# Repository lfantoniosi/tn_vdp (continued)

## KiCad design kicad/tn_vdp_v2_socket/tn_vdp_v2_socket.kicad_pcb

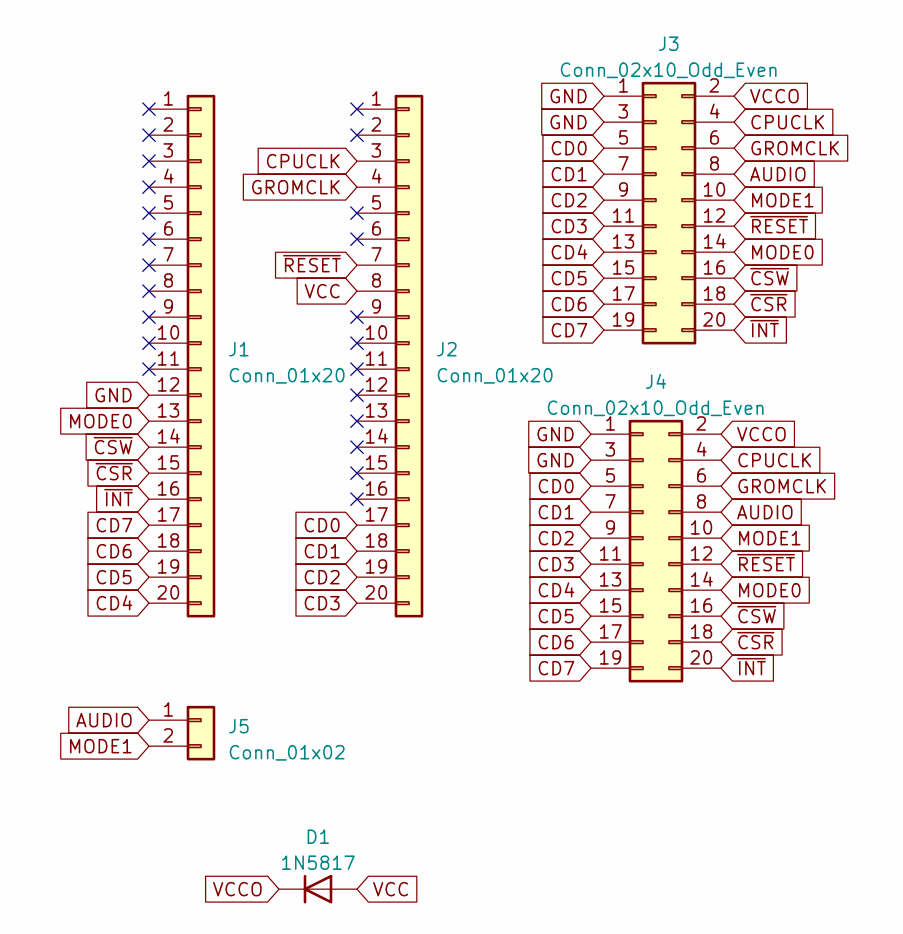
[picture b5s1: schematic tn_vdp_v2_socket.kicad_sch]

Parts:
D1: 1N5817; D_DO-41_SOD81_P10.16mm_Horizontal
J1, J2: Conn_01x20; PinHeader_1x20_P2.54mm_Vertical
J3, J4: Conn_02x10_Odd_Even; PinHeader_2x10_P2.54mm_Vertical
J5: Conn_01x02; PinHeader_1x02_P2.54mm_Vertical

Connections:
AUDIO: J3.8, J4.8, J5.1
CD0: J2.17, J3.5, J4.5
CD1: J2.18, J3.7, J4.7
CD2: J2.19, J3.9, J4.9
CD3: J2.20, J3.11, J4.11
CD4: J1.20, J3.13, J4.13
CD5: J1.19, J3.15, J4.15
CD6: J1.18, J3.17, J4.17
CD7: J1.17, J3.19, J4.19
CPUCLK: J2.3, J3.4, J4.4
GND: J1.12, J3.1, J3.3, J4.1, J4.3
GROMCLK: J2.4, J3.6, J4.6
MODE0: J1.13, J3.14, J4.14
MODE1: J3.10, J4.10, J5.2
VCC: D1.2 (A), J2.8
VCCO: D1.1 (K), J3.2, J4.2
~CSR: J1.15, J3.18, J4.18
~CSW: J1.14, J3.16, J4.16
~INT: J1.16, J3.20, J4.20
~RESET: J2.7, J3.12, J4.12

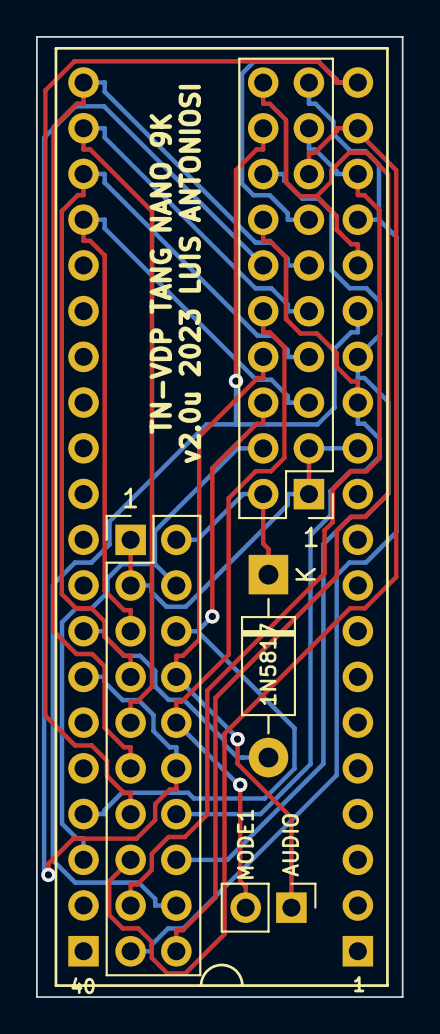
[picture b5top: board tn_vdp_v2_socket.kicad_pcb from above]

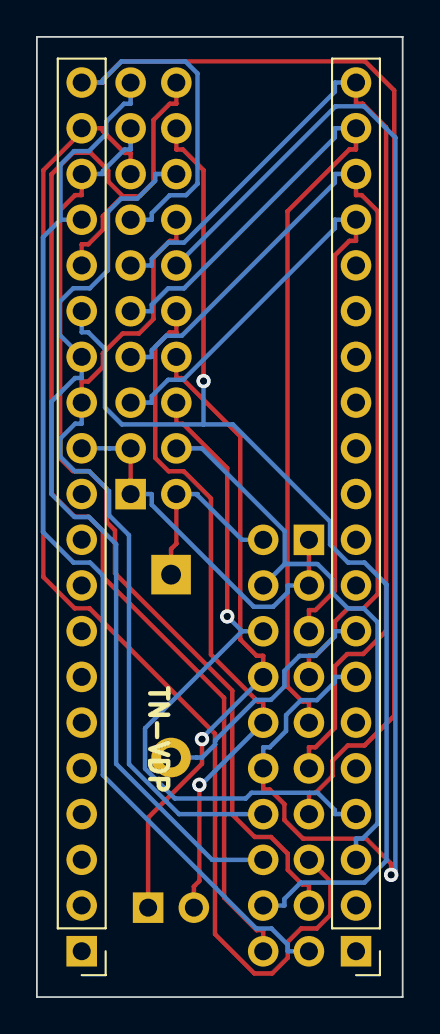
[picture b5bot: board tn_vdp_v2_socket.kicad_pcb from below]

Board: 2 copper layers, 20.3 x 53.3 mm, 6 parts (2 on the bottom side), 20 nets.

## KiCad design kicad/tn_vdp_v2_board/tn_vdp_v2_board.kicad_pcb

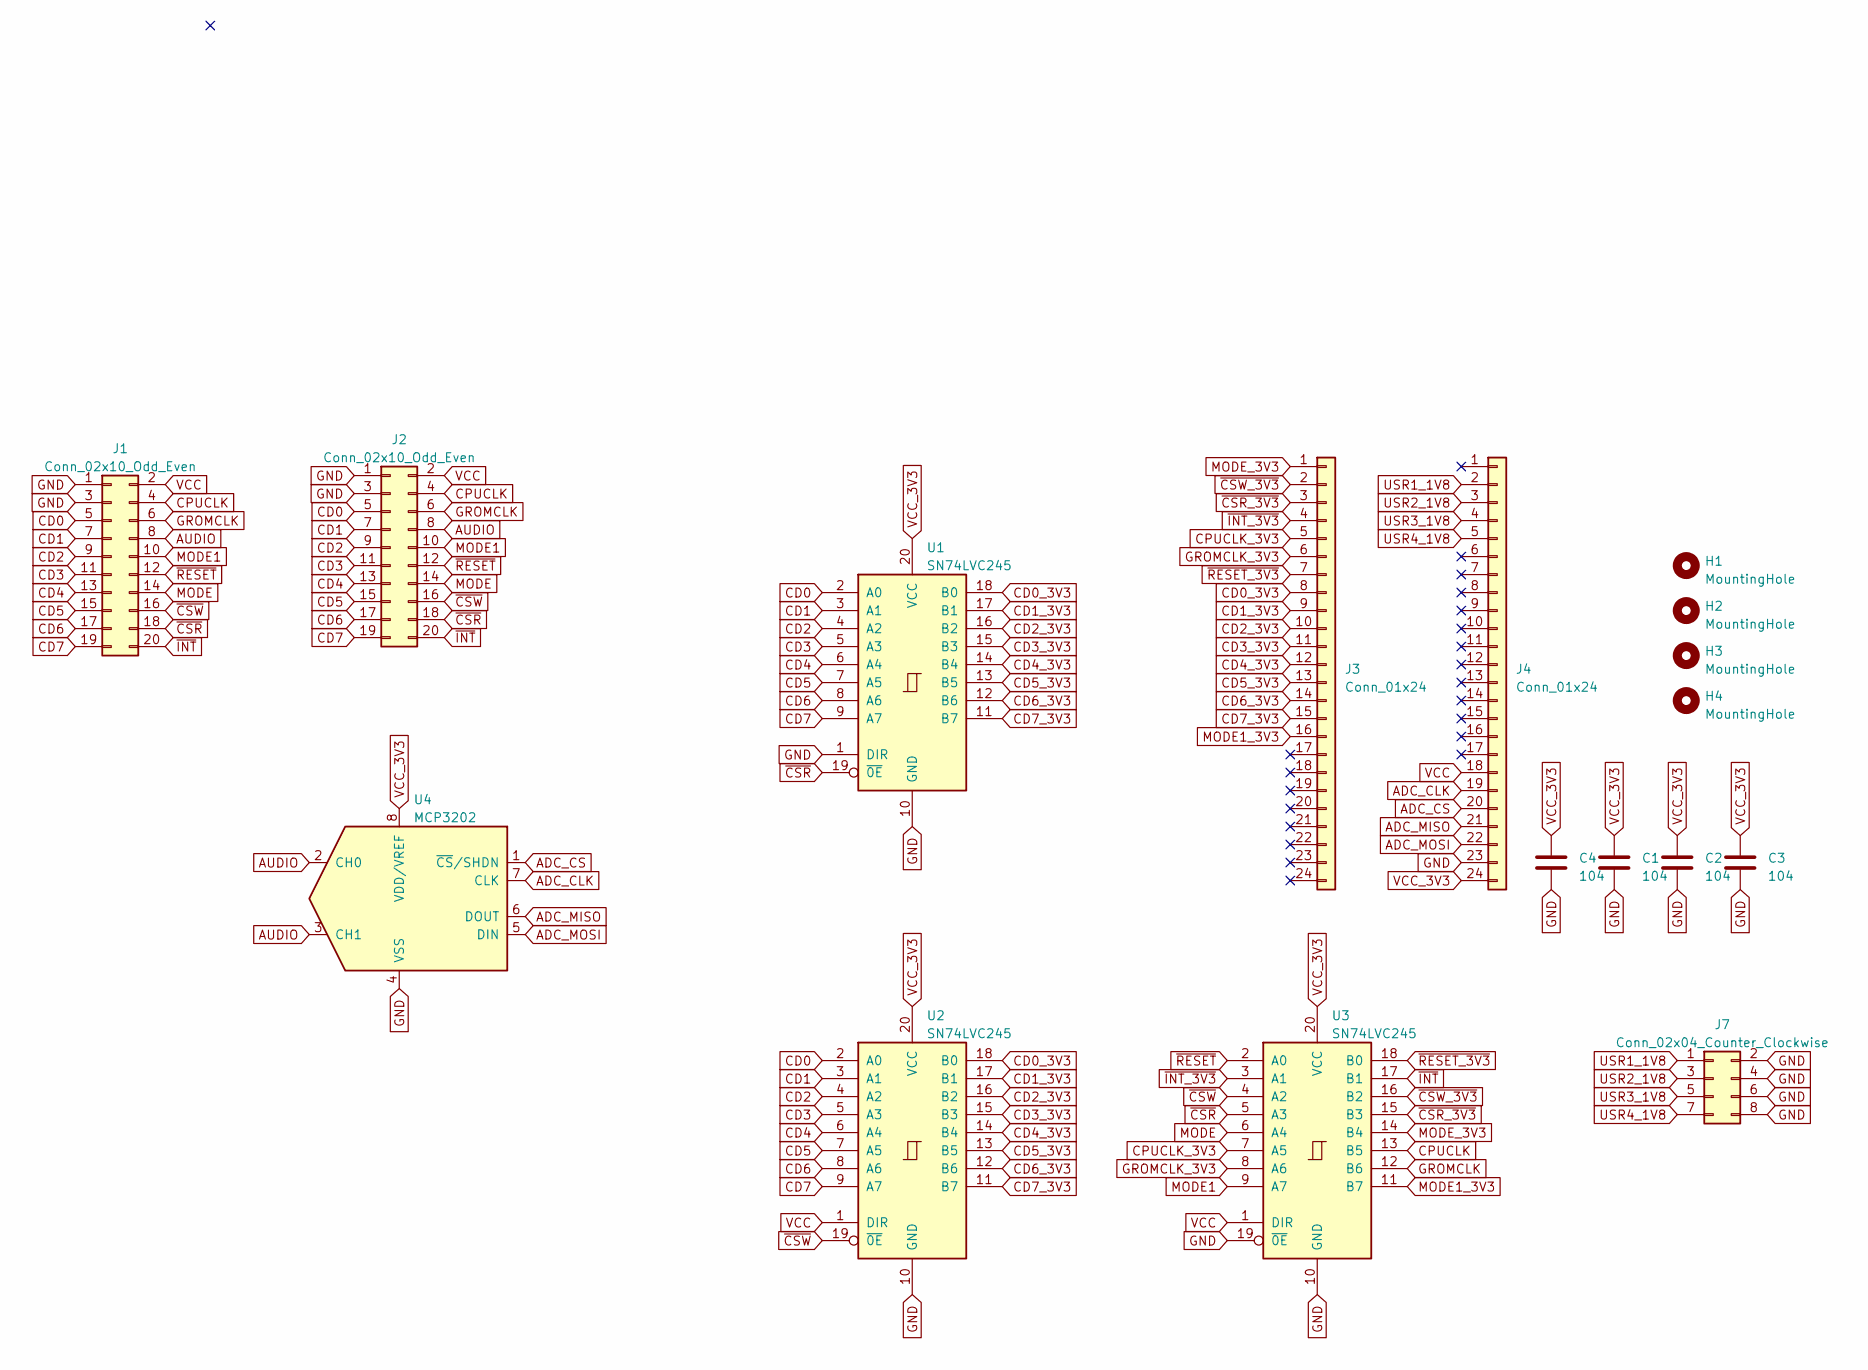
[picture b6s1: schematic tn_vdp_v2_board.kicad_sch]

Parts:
C1, C2, C3, C4: 104; C_Disc_D5.0mm_W2.5mm_P2.50mm
H1, H2, H3, H4: MountingHole; MountingHole_2.2mm_M2_ISO7380_Pad
J1, J2: Conn_02x10_Odd_Even; PinHeader_2x10_P2.54mm_Vertical
J3, J4: Conn_01x24; PinSocket_1x24_P2.54mm_Vertical
J7: Conn_02x04_Counter_Clockwise; PinHeader_2x04_P2.54mm_Vertical
U1, U2, U3: SN74LVC245; DIP-20_W7.62mm_Socket_LongPads
U4: MCP3202; DIP-8_W7.62mm_LongPads

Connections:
ADC_CLK: J4.19, U4.7 (CLK)
ADC_CS: J4.20, U4.1 (~CS/SHDN)
ADC_MISO: J4.21, U4.6 (DOUT)
ADC_MOSI: J4.22, U4.5 (DIN)
AUDIO: J1.8, J2.8, U4.2 (CH0), U4.3 (CH1)
CD0: J1.5, J2.5, U1.2 (A0), U2.2 (A0)
CD0_3V3: J3.8, U1.18 (B0), U2.18 (B0)
CD1: J1.7, J2.7, U1.3 (A1), U2.3 (A1)
CD1_3V3: J3.9, U1.17 (B1), U2.17 (B1)
CD2: J1.9, J2.9, U1.4 (A2), U2.4 (A2)
CD2_3V3: J3.10, U1.16 (B2), U2.16 (B2)
CD3: J1.11, J2.11, U1.5 (A3), U2.5 (A3)
CD3_3V3: J3.11, U1.15 (B3), U2.15 (B3)
CD4: J1.13, J2.13, U1.6 (A4), U2.6 (A4)
CD4_3V3: J3.12, U1.14 (B4), U2.14 (B4)
CD5: J1.15, J2.15, U1.7 (A5), U2.7 (A5)
CD5_3V3: J3.13, U1.13 (B5), U2.13 (B5)
CD6: J1.17, J2.17, U1.8 (A6), U2.8 (A6)
CD6_3V3: J3.14, U1.12 (B6), U2.12 (B6)
CD7: J1.19, J2.19, U1.9 (A7), U2.9 (A7)
CD7_3V3: J3.15, U1.11 (B7), U2.11 (B7)
CPUCLK: J1.4, J2.4, U3.13 (B5)
CPUCLK_3V3: J3.5, U3.7 (A5)
GND: C1.2, C2.2, C3.2, C4.2, J1.1, J1.3, J2.1, J2.3, J4.23, J7.2, J7.4, J7.6, J7.8, U1.1 (DIR), U1.10 (GND), U2.10 (GND), U3.10 (GND), U3.19 (~0E), U4.4 (VSS)
GROMCLK: J1.6, J2.6, U3.12 (B6)
GROMCLK_3V3: J3.6, U3.8 (A6)
MODE: J1.14, J2.14, U3.6 (A4)
MODE1: J1.10, J2.10, U3.9 (A7)
MODE1_3V3: J3.16, U3.11 (B7)
MODE_3V3: J3.1, U3.14 (B4)
USR1_1V8: J4.2, J7.1
USR2_1V8: J4.3, J7.3
USR3_1V8: J4.4, J7.5
USR4_1V8: J4.5, J7.7
VCC: J1.2, J2.2, J4.18, U2.1 (DIR), U3.1 (DIR)
VCC_3V3: C1.1, C2.1, C3.1, C4.1, J4.24, U1.20 (VCC), U2.20 (VCC), U3.20 (VCC), U4.8 (VDD/VREF)
~CSR_3V3: J3.3, U3.15 (B3)
~CSR: J1.18, J2.18, U1.19 (~0E), U3.5 (A3)
~CSW_3V3: J3.2, U3.16 (B2)
~CSW: J1.16, J2.16, U2.19 (~0E), U3.4 (A2)
~INT_3V3: J3.4, U3.3 (A1)
~INT: J1.20, J2.20, U3.17 (B1)
~RESET_3V3: J3.7, U3.18 (B0)
~RESET: J1.12, J2.12, U3.2 (A0)

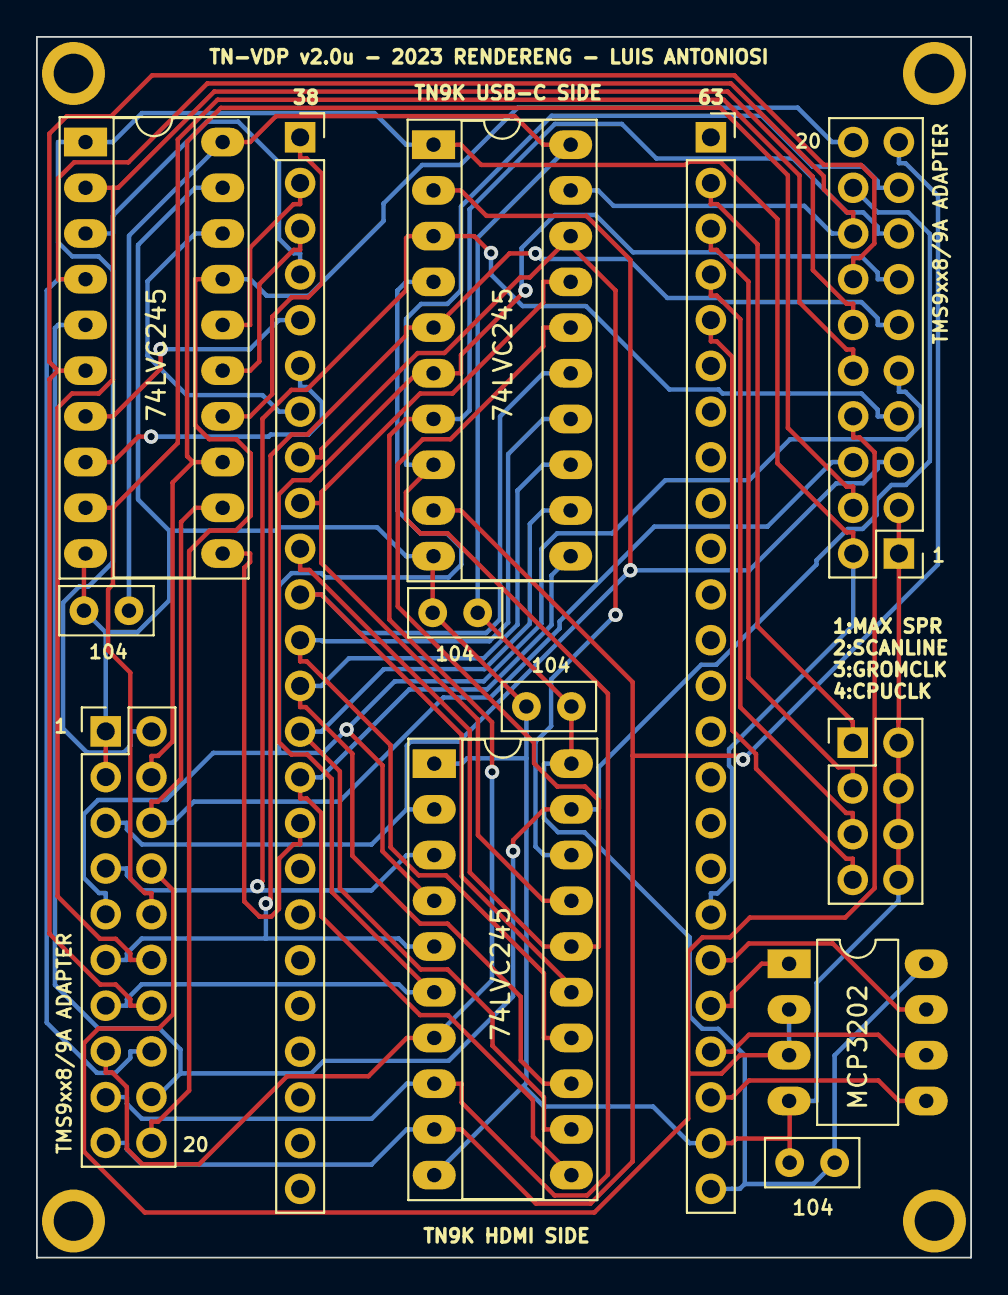
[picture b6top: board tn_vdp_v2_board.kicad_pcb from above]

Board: 2 copper layers, 51.9 x 67.8 mm, 17 parts (0 on the bottom side), 44 nets.

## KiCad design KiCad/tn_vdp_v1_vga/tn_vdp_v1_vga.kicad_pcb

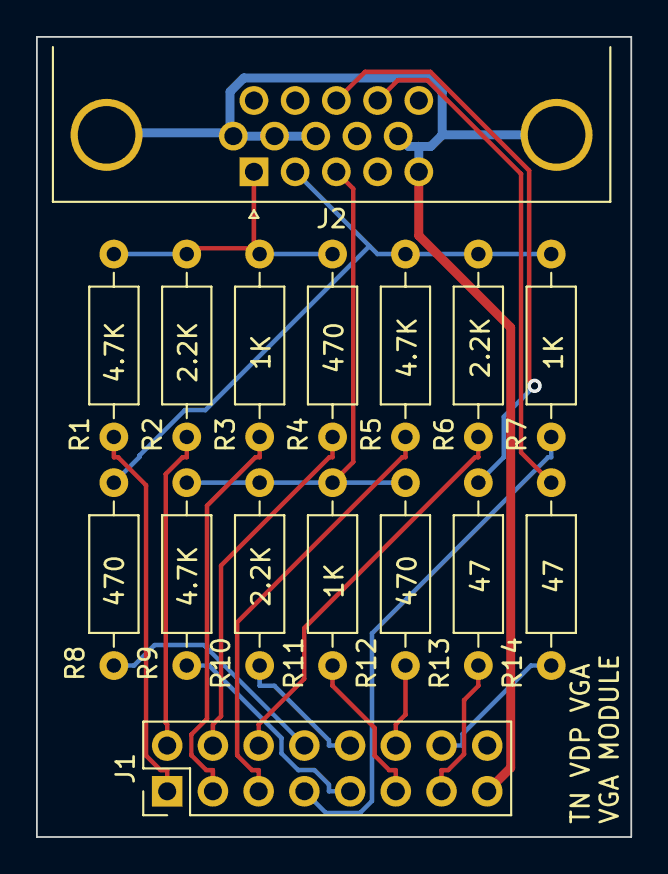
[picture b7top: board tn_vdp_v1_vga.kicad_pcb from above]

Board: 2 copper layers, 33.0 x 44.5 mm, 16 parts (0 on the bottom side), 20 nets.

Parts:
J1: Conn_02x08_Odd_Even; PinHeader_2x08_P2.54mm_Vertical
J2: DE15_Receptacle_HighDensity_MountingHoles; DSUB-15-HD_Female_Horizontal_P2.29x1.98mm_EdgePinOffset3.03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
R1, R5, R9: 4.7K; R_Axial_DIN0207_L6.3mm_D2.5mm_P10.16mm_Horizontal
R2, R6, R10: 2.2K; R_Axial_DIN0207_L6.3mm_D2.5mm_P10.16mm_Horizontal
R3, R7, R11: 1K; R_Axial_DIN0207_L6.3mm_D2.5mm_P10.16mm_Horizontal
R4, R8, R12: 470; R_Axial_DIN0207_L6.3mm_D2.5mm_P10.16mm_Horizontal
R13, R14: 47; R_Axial_DIN0207_L6.3mm_D2.5mm_P10.16mm_Horizontal

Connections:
B0_3V3: J1.9, R9.2
B1_3V3: J1.10, R10.2
B2_3V3: J1.11, R11.2
B3_3V3: J1.12, R12.2
BLUE: J2.3, R9.1, R10.1, R11.1, R12.1
G0_3V3: J1.5, R5.2
G1_3V3: J1.6, R6.2
G2_3V3: J1.7, R7.2
G3_3V3: J1.8, R8.2
GND: J1.15, J2.0, J2.5, J2.6, J2.7, J2.8, J2.10
GREEN: J2.2, R5.1, R6.1, R7.1, R8.1
HSYNC: J2.13, R13.1
HS_3V3: J1.13, R13.2
R0_3V3: J1.1, R1.2
R1_3V3: J1.2, R2.2
R2_3V3: J1.3, R3.2
R3_3V3: J1.4, R4.2
RED: J2.1, R1.1, R2.1, R3.1, R4.1
VSYNC: J2.14, R14.1
VS_3V3: J1.14, R14.2

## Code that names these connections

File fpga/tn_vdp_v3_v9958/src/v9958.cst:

//Copyright (C)2014-2023 Gowin Semiconductor Corporation.
//All rights reserved. 
//File Title: Physical Constraints file
//GOWIN Version: 1.9.8.11 Education
//Part Number: GW2AR-LV18QN88C8/I7
//Device: GW2AR-18
//Device Version: C
//Created Time: Wed 07 19 21:03:46 2023

IO_LOC "clk" 4;
IO_PORT "clk" PULL_MODE=UP;

IO_LOC "clk_50" 10;
IO_PORT "clk_50" PULL_MODE=UP;

IO_LOC "clk_125" 11;
IO_PORT "clk_125" PULL_MODE=UP;

IO_LOC "s1" 88;
IO_PORT "s1" PULL_MODE=DOWN;

IO_LOC "adc_mosi" 52;
IO_PORT "adc_mosi" IO_TYPE=LVCMOS33 PULL_MODE=DOWN DRIVE=16;
IO_LOC "adc_cs" 71;
IO_PORT "adc_cs" IO_TYPE=LVCMOS33 PULL_MODE=DOWN DRIVE=16;
IO_LOC "adc_clk" 72;
IO_PORT "adc_clk" IO_TYPE=LVCMOS33 PULL_MODE=DOWN DRIVE=16;
IO_LOC "adc_miso" 53;
IO_PORT "adc_miso" IO_TYPE=LVCMOS33 PULL_MODE=DOWN;

IO_LOC "gromclk" 30;
IO_PORT "gromclk" IO_TYPE=LVCMOS33 PULL_MODE=UP DRIVE=16;
IO_LOC "cpuclk" 29;
IO_PORT "cpuclk" IO_TYPE=LVCMOS33 PULL_MODE=UP DRIVE=16;

IO_LOC "csr_n" 25;
IO_PORT "csr_n" IO_TYPE=LVCMOS33 PULL_MODE=UP;
IO_LOC "csw_n" 28;
IO_PORT "csw_n" IO_TYPE=LVCMOS33 PULL_MODE=UP;
IO_LOC "mode[1]" 86;
IO_PORT "mode[1]" IO_TYPE=LVCMOS33 PULL_MODE=DOWN;
IO_LOC "mode[0]" 27;
IO_PORT "mode[0]" IO_TYPE=LVCMOS33 PULL_MODE=DOWN;
IO_LOC "reset_n" 31;
IO_PORT "reset_n" IO_TYPE=LVCMOS33 PULL_MODE=UP;
IO_LOC "int_n" 26;
IO_PORT "int_n" IO_TYPE=LVCMOS33 PULL_MODE=UP DRIVE=16;

IO_LOC "cd[7]" 42;
IO_PORT "cd[7]" IO_TYPE=LVCMOS33 PULL_MODE=NONE DRIVE=16;
IO_LOC "cd[6]" 41;
IO_PORT "cd[6]" IO_TYPE=LVCMOS33 PULL_MODE=NONE DRIVE=16;
IO_LOC "cd[5]" 56;
IO_PORT "cd[5]" IO_TYPE=LVCMOS33 PULL_MODE=NONE DRIVE=16;
IO_LOC "cd[4]" 54;
IO_PORT "cd[4]" IO_TYPE=LVCMOS33 PULL_MODE=NONE DRIVE=16;
IO_LOC "cd[3]" 51;
IO_PORT "cd[3]" IO_TYPE=LVCMOS33 PULL_MODE=NONE DRIVE=16;
IO_LOC "cd[2]" 48;
IO_PORT "cd[2]" IO_TYPE=LVCMOS33 PULL_MODE=NONE DRIVE=16;
IO_LOC "cd[1]" 55;
IO_PORT "cd[1]" IO_TYPE=LVCMOS33 PULL_MODE=NONE DRIVE=16;
IO_LOC "cd[0]" 49;
IO_PORT "cd[0]" IO_TYPE=LVCMOS33 PULL_MODE=NONE DRIVE=16;

IO_LOC "cpuclk_ena_n" 18;
IO_PORT "cpuclk_ena_n" IO_TYPE=LVCMOS33 PULL_MODE=UP;
IO_LOC "gromclk_ena_n" 19;
IO_PORT "gromclk_ena_n" IO_TYPE=LVCMOS33 PULL_MODE=UP;
IO_LOC "scanlin_n" 20;
IO_PORT "scanlin_n" IO_TYPE=LVCMOS33 PULL_MODE=UP;
IO_LOC "maxspr_n" 17;
IO_PORT "maxspr_n" IO_TYPE=LVCMOS33 PULL_MODE=UP;

IO_LOC "tmds_data_p[0]" 35,36;
IO_PORT "tmds_data_p[0]" IO_TYPE=LVCMOS33D PULL_MODE=NONE DRIVE=16;
IO_LOC "tmds_data_p[1]" 37,38;
IO_PORT "tmds_data_p[1]" IO_TYPE=LVCMOS33D PULL_MODE=NONE DRIVE=16;
IO_LOC "tmds_data_p[2]" 39,40;
IO_PORT "tmds_data_p[2]" IO_TYPE=LVCMOS33D PULL_MODE=NONE DRIVE=16;
IO_LOC "tmds_clk_p" 33,34;
IO_PORT "tmds_clk_p" IO_TYPE=LVCMOS33D PULL_MODE=NONE DRIVE=16;

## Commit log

2023-05-01 complimentary initial commit
2023-05-01 Update README.md
    updated readme
2023-05-02 Update rtl_parser_arg.json
    fix project
2023-05-02 adding FAT version
2023-05-02 update silk on fat board
2023-05-04 fat board
2023-05-07 remove the bufg and set optimization flags
2023-05-12 more images
2023-05-13 fixing power on gromclk
    NABU PC nows seems to boot normally from cold-boot
2023-05-14 images
2023-05-16 nabu backplate model
2023-05-19 faster power on
2023-05-20 rename files for matching case
2023-05-20 enable gromclk and cpuclk before por
2023-05-20 Update README.md with pointer to openFPGALoader
2023-05-21 Add tcl script to support command-line builds
    Use 'gw_sh tn9k_f18A.tcl' to build the bitstream.
2023-05-21 remove power on wait and disable user SPI lines
    hdmi sink seems to conflict with spi user at startup causing the f118 to slow. I have no idea but disabling them seems to solve the boot time with hdmi
2023-05-21 booting code faster
    adding compress to the code, loads faster
    remove drive constraints
    restoring spi lines
2023-05-22 save work
2023-05-22 SMD version
2023-05-22 re-add original board
2023-05-22 Version H1 sent to aisler
2023-05-22 rename compact version files
2023-05-22 silkscreen tweaks
2023-05-22 Schematics PDF
2023-05-22 Add diode to prevent host being powered from TN9k
    HDMI has a +5V supply line that could halfway power up the TI-99/4A
2023-05-22 Update gerbers
2023-05-22 README.md edits
2023-05-22 README work
2023-05-22 update FAT board for the diode
2023-05-22 update original board adding diode
2023-05-23 Fix my name
2023-05-24 Add BOM
2023-05-31 rebrand to TN VDP
2023-05-31 rebrand of the compact version + license update
2023-05-31 link to F18A info
2023-06-03 HDMI AUDIO
    Board V2
    Code V2 for V9918
    New core V9958 (V2)
2023-06-04 v9958 use 525p mode instead
2023-06-05 fix vga output in v1
2023-06-06 add maxspr swtich to v9958
2023-06-06 invert maxspr jumper signal
2023-06-07 fix sprite multiplexing
2023-06-08 center screen
2023-06-09 16 sprites per line
2023-06-09 fix timings on 9958
2023-06-10 revert the 16 sprite line fix screen split
2023-06-11 new TN-VDP logo
2023-06-11 new logo
2023-06-11 moving stuff around
2023-06-11 moving stuff
2023-06-11 sprite disable fix
2023-06-12 add pal mode 576p
2023-06-12 missing last commit
2023-06-12 missing files
2023-06-13 interlace fixes
2023-07-01 V3 Tang 20k Board and FPGA
2023-07-04 re-committing v2
2023-07-11 V2 9918: reset hdmi when video desyncs
2023-07-11 fix v2 9958 sync
2023-07-11 fix v3
2023-07-12 better cpuclk on v3
2023-07-14 Improving SDRAM access to 108mhz, audio adjustments
2023-07-14 audio adjust
2023-07-15 adding low pass filter to audio + other improvements
2023-07-16 improving stability and precision of clock dividers
2023-07-17 new clocks 3.58Mhz !!!
2023-07-18 revert some clk changes + add support to v9958 socket
2023-07-19 put b_window back, trigger h
2023-07-20 stability fixres plus interrupt
2023-07-20 V9958 Socket + New V3 Board (audio fix + cinch connector)
2023-07-21 improved clock 3.580Mhz + interrupt timers corrected
2023-07-23 Adjust vertical retraces + SBB running fine
2023-07-23 revert CD (9958 prototype got it reversed)
2023-07-24 vertical and horizontal sync tunning
2023-07-29 fixing overscan
2023-07-29 interrupt
2023-07-30 interrupt boundary
2023-07-31 final tuning for UR and SBB
2023-07-31 fix aleste 2....
2023-08-12 left mask bug
    msx2+ logo now works
2023-08-28 v3 last board last version
2023-12-02 Create tn_vdp_v3_v995_debug_mode.fs
    adding debug mode core
2023-12-02 fix interrupt line as open collector
